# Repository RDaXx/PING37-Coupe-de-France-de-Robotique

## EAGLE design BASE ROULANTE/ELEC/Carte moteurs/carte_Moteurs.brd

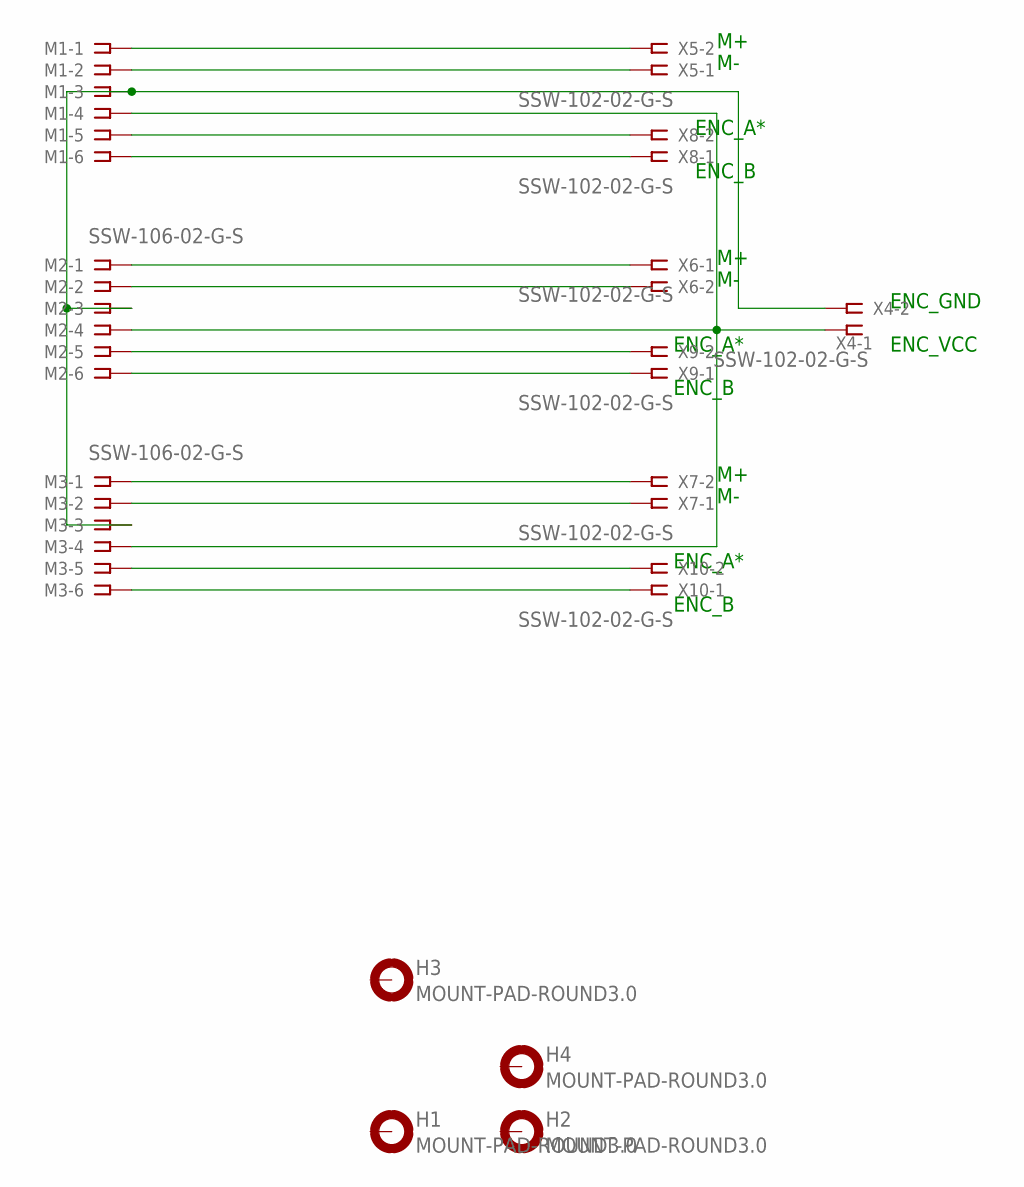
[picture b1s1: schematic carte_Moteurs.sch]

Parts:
H1, H2, H3, H4: MOUNT-PAD-ROUND3.0; 3,0-PAD
M1: SSW-106-02-G-S; MPN Motor1
M2, M3: SSW-106-02-G-S
X4, X5, X6, X7, X8, X9, X10: SSW-102-02-G-S

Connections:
unnamed: M1.1, X5.2
unnamed: M1.2, X5.1
unnamed: M2.1, X6.1
unnamed: M2.2, X6.2
unnamed: M3.1, X7.2
unnamed: M3.2, X7.1
unnamed: M1.6, X8.1
unnamed: M1.5, X8.2
unnamed: M2.5, X9.2
unnamed: M2.6, X9.1
unnamed: M3.5, X10.2
unnamed: M3.6, X10.1
unnamed: M1.3, M2.3, M3.3, X4.2
unnamed: M1.4, M2.4, M3.4, X4.1

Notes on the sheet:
ENC_GND
ENC_VCC
ENC_A*
ENC_B

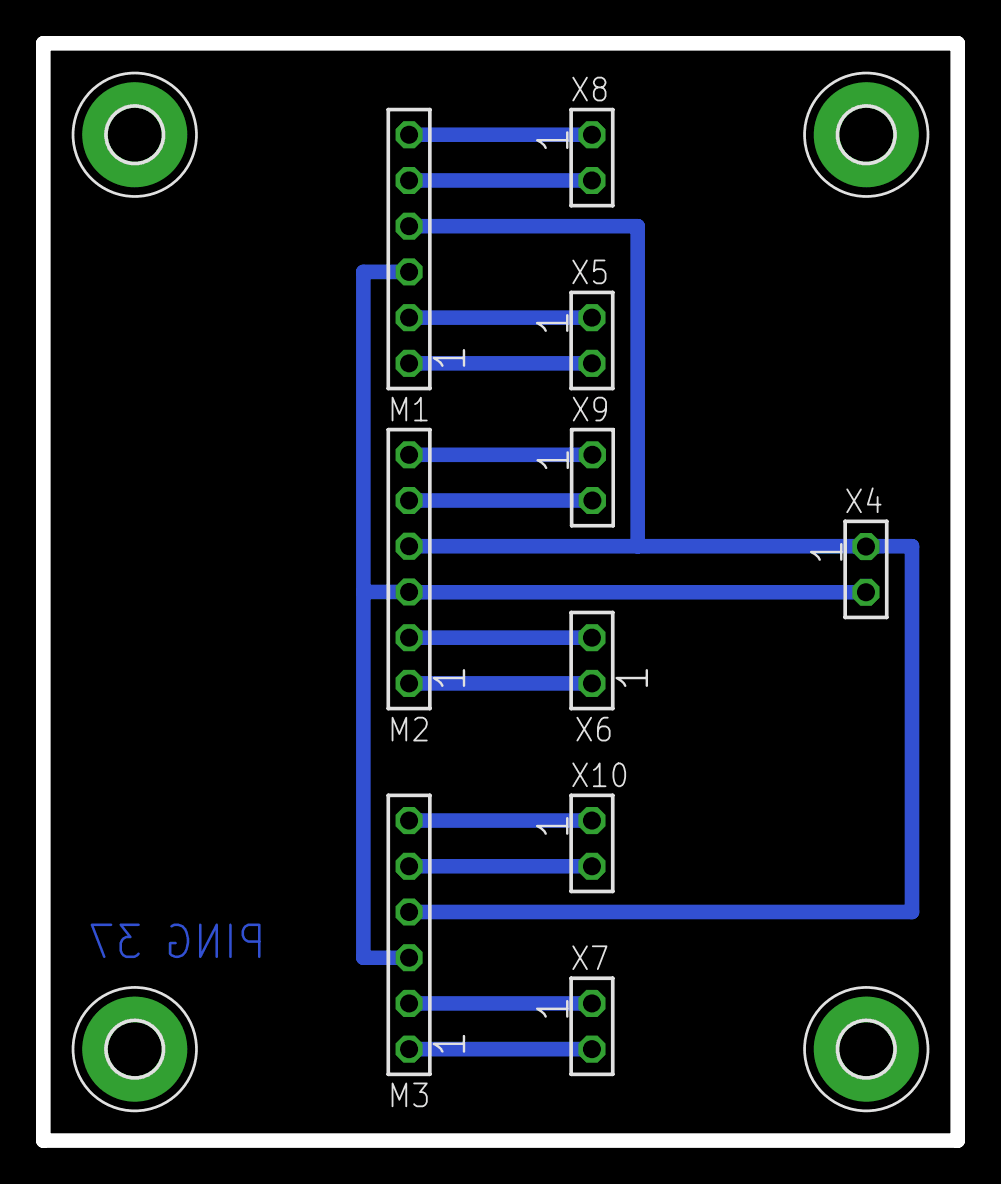
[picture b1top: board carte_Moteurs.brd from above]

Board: 2 copper layers, 50.8 x 61.0 mm, 14 parts (0 on the bottom side), 14 nets.

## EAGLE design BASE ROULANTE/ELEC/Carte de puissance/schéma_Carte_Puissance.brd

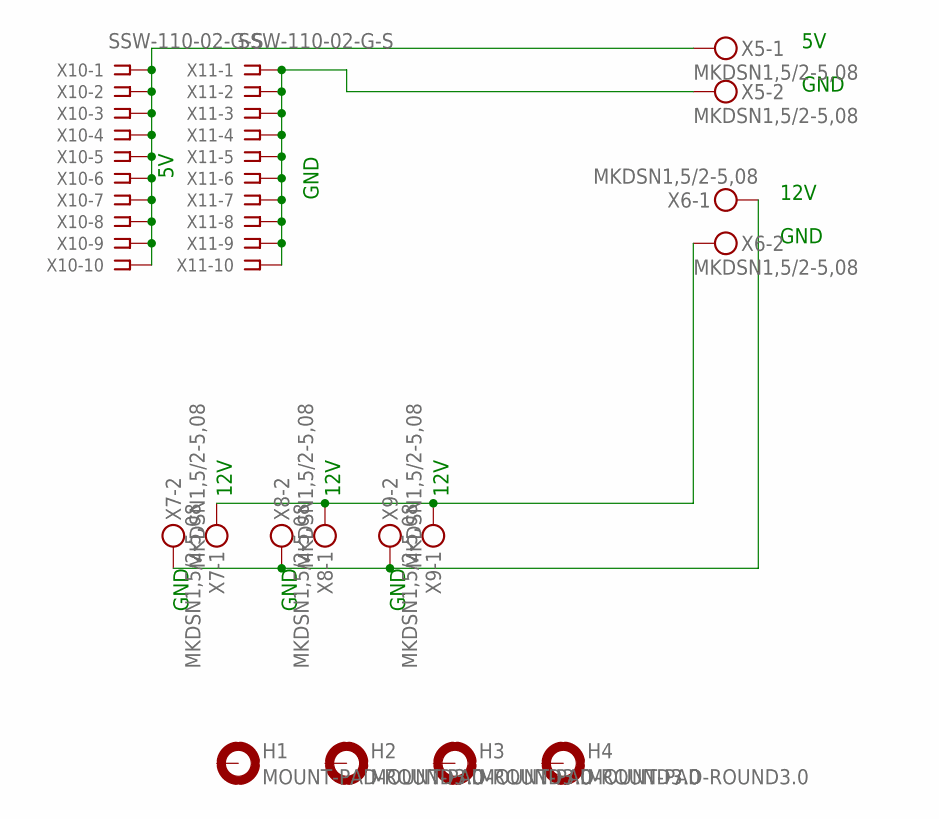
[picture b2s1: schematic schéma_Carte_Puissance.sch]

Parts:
H1, H2, H3, H4: MOUNT-PAD-ROUND3.0; 3,0-PAD
X5, X6, X7, X8, X9: MKDSN1,5/2-5,08
X10, X11: SSW-110-02-G-S

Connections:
unnamed: X5.1, X10.1, X10.2, X10.3, X10.4, X10.5, X10.6, X10.7, X10.8, X10.9, X10.10
unnamed: X5.2, X11.1, X11.2, X11.3, X11.4, X11.5, X11.6, X11.7, X11.8, X11.9, X11.10
unnamed: X6.2, X7.1, X8.1, X9.1
unnamed: X6.1, X7.2, X8.2, X9.2

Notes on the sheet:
GND
12V

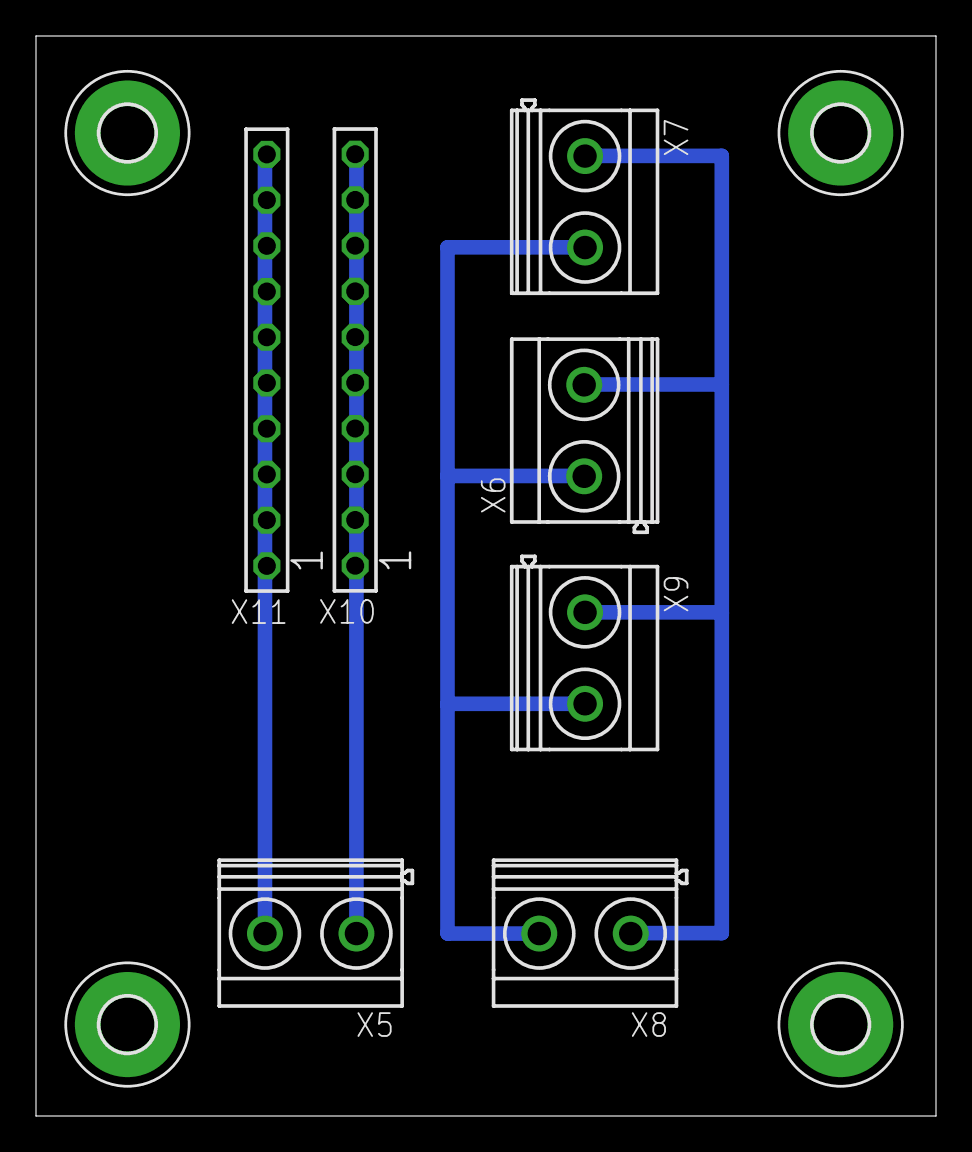
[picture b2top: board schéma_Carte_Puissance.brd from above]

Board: 2 copper layers, 50.0 x 60.0 mm, 11 parts (0 on the bottom side), 4 nets.

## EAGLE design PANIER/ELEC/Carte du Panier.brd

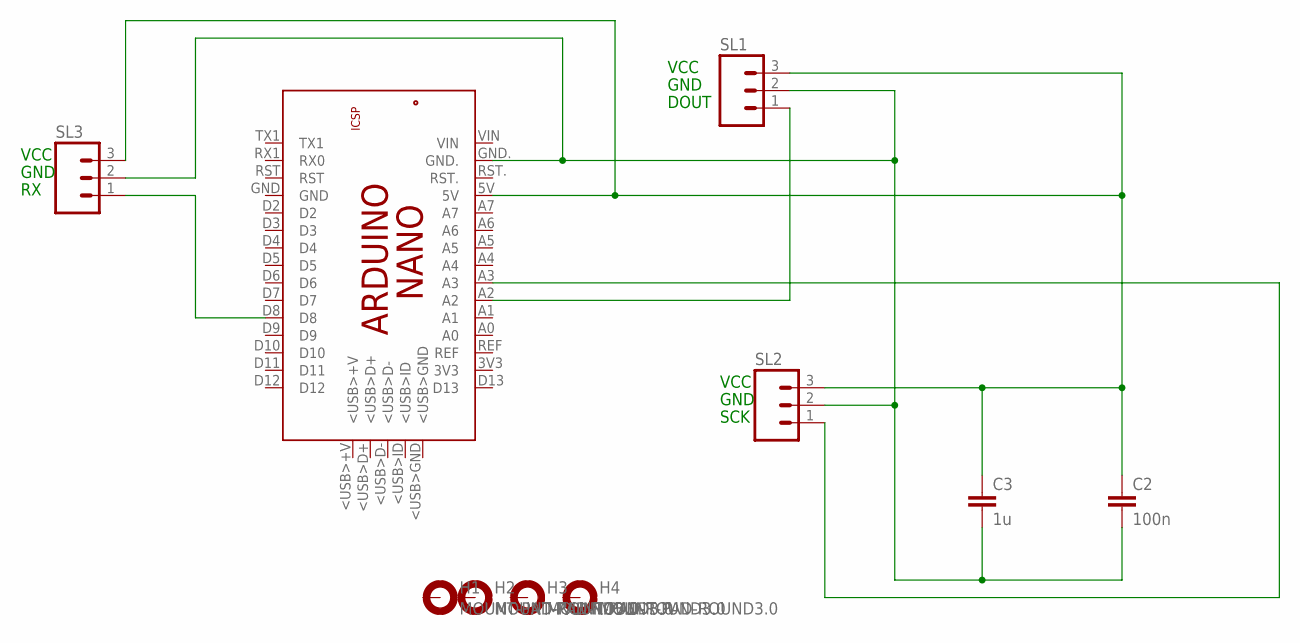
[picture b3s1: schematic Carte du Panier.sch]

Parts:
C2: 100n; C025-024X044
C3: 1u; C025-024X044
H1, H2, H3, H4: MOUNT-PAD-ROUND3.0; 3,0-PAD
PCB1: ARDUINO_NANO
SL1, SL2, SL3: M03; 03P

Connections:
unnamed: PCB1.D8, SL3.1
unnamed: PCB1.A3, SL2.1
unnamed: C2.2, C3.2, PCB1.GND., SL1.2, SL2.2, SL3.2
unnamed: C2.1, C3.1, PCB1.5V, SL1.3, SL2.3, SL3.3
unnamed: PCB1.A2, SL1.1

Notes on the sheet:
VCC
GND
DOUT
SCK

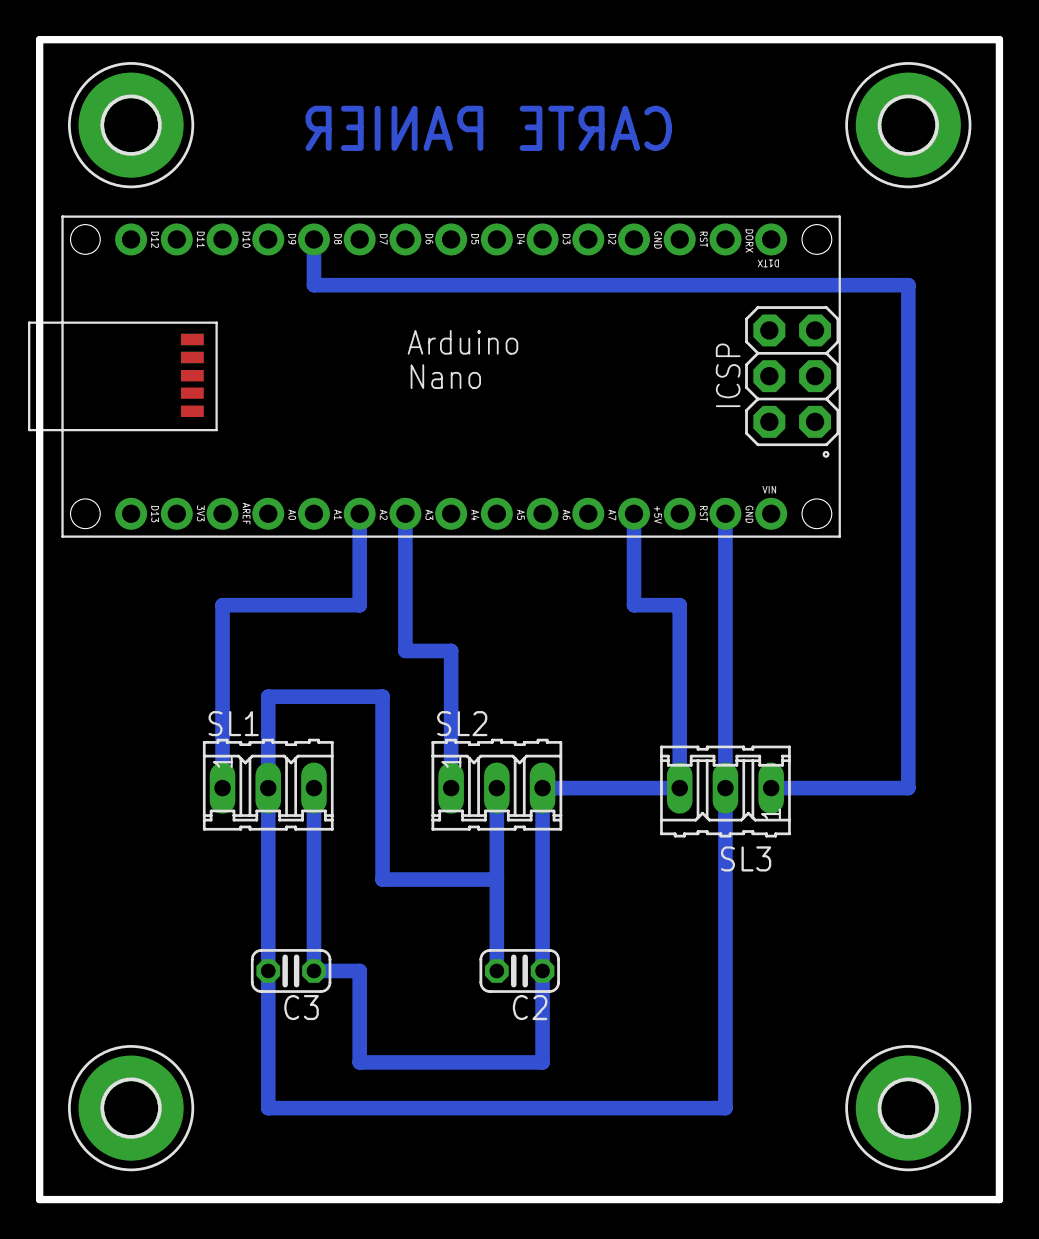
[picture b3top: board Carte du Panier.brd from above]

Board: 2 copper layers, 53.3 x 64.4 mm, 10 parts (0 on the bottom side), 5 nets.
